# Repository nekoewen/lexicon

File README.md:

# Lexicon 65% Writing Keyboard

The Lexicon (or if you prefer the Lexicon 69 or the Cluney №3) is a 65% keyboard designed for writing prose, available from [WeirdLittleKeebs](https://www.weirdlittlekeebs.com/). With an extensive collection of shortcuts for words, formatting commands, and extended punctuation, this keyboard changes the experience of writing while maintaining a standard QWERTY layout. Check out the User's Guide to see how its unique features work.

## [Build Guide](https://github.com/nekoewen/lexicon/blob/main/Lexicon%20Build%20Guide.pdf)
If you purchased a set of Lexicon PCB and plates, this guide will walk you through the assembly process.

## [User's Guide](https://github.com/nekoewen/lexicon/blob/main/Lexicon%20User's%20Guide.pdf)
Once you have a Lexicon ready to use, this guide explains all of its features in detail.

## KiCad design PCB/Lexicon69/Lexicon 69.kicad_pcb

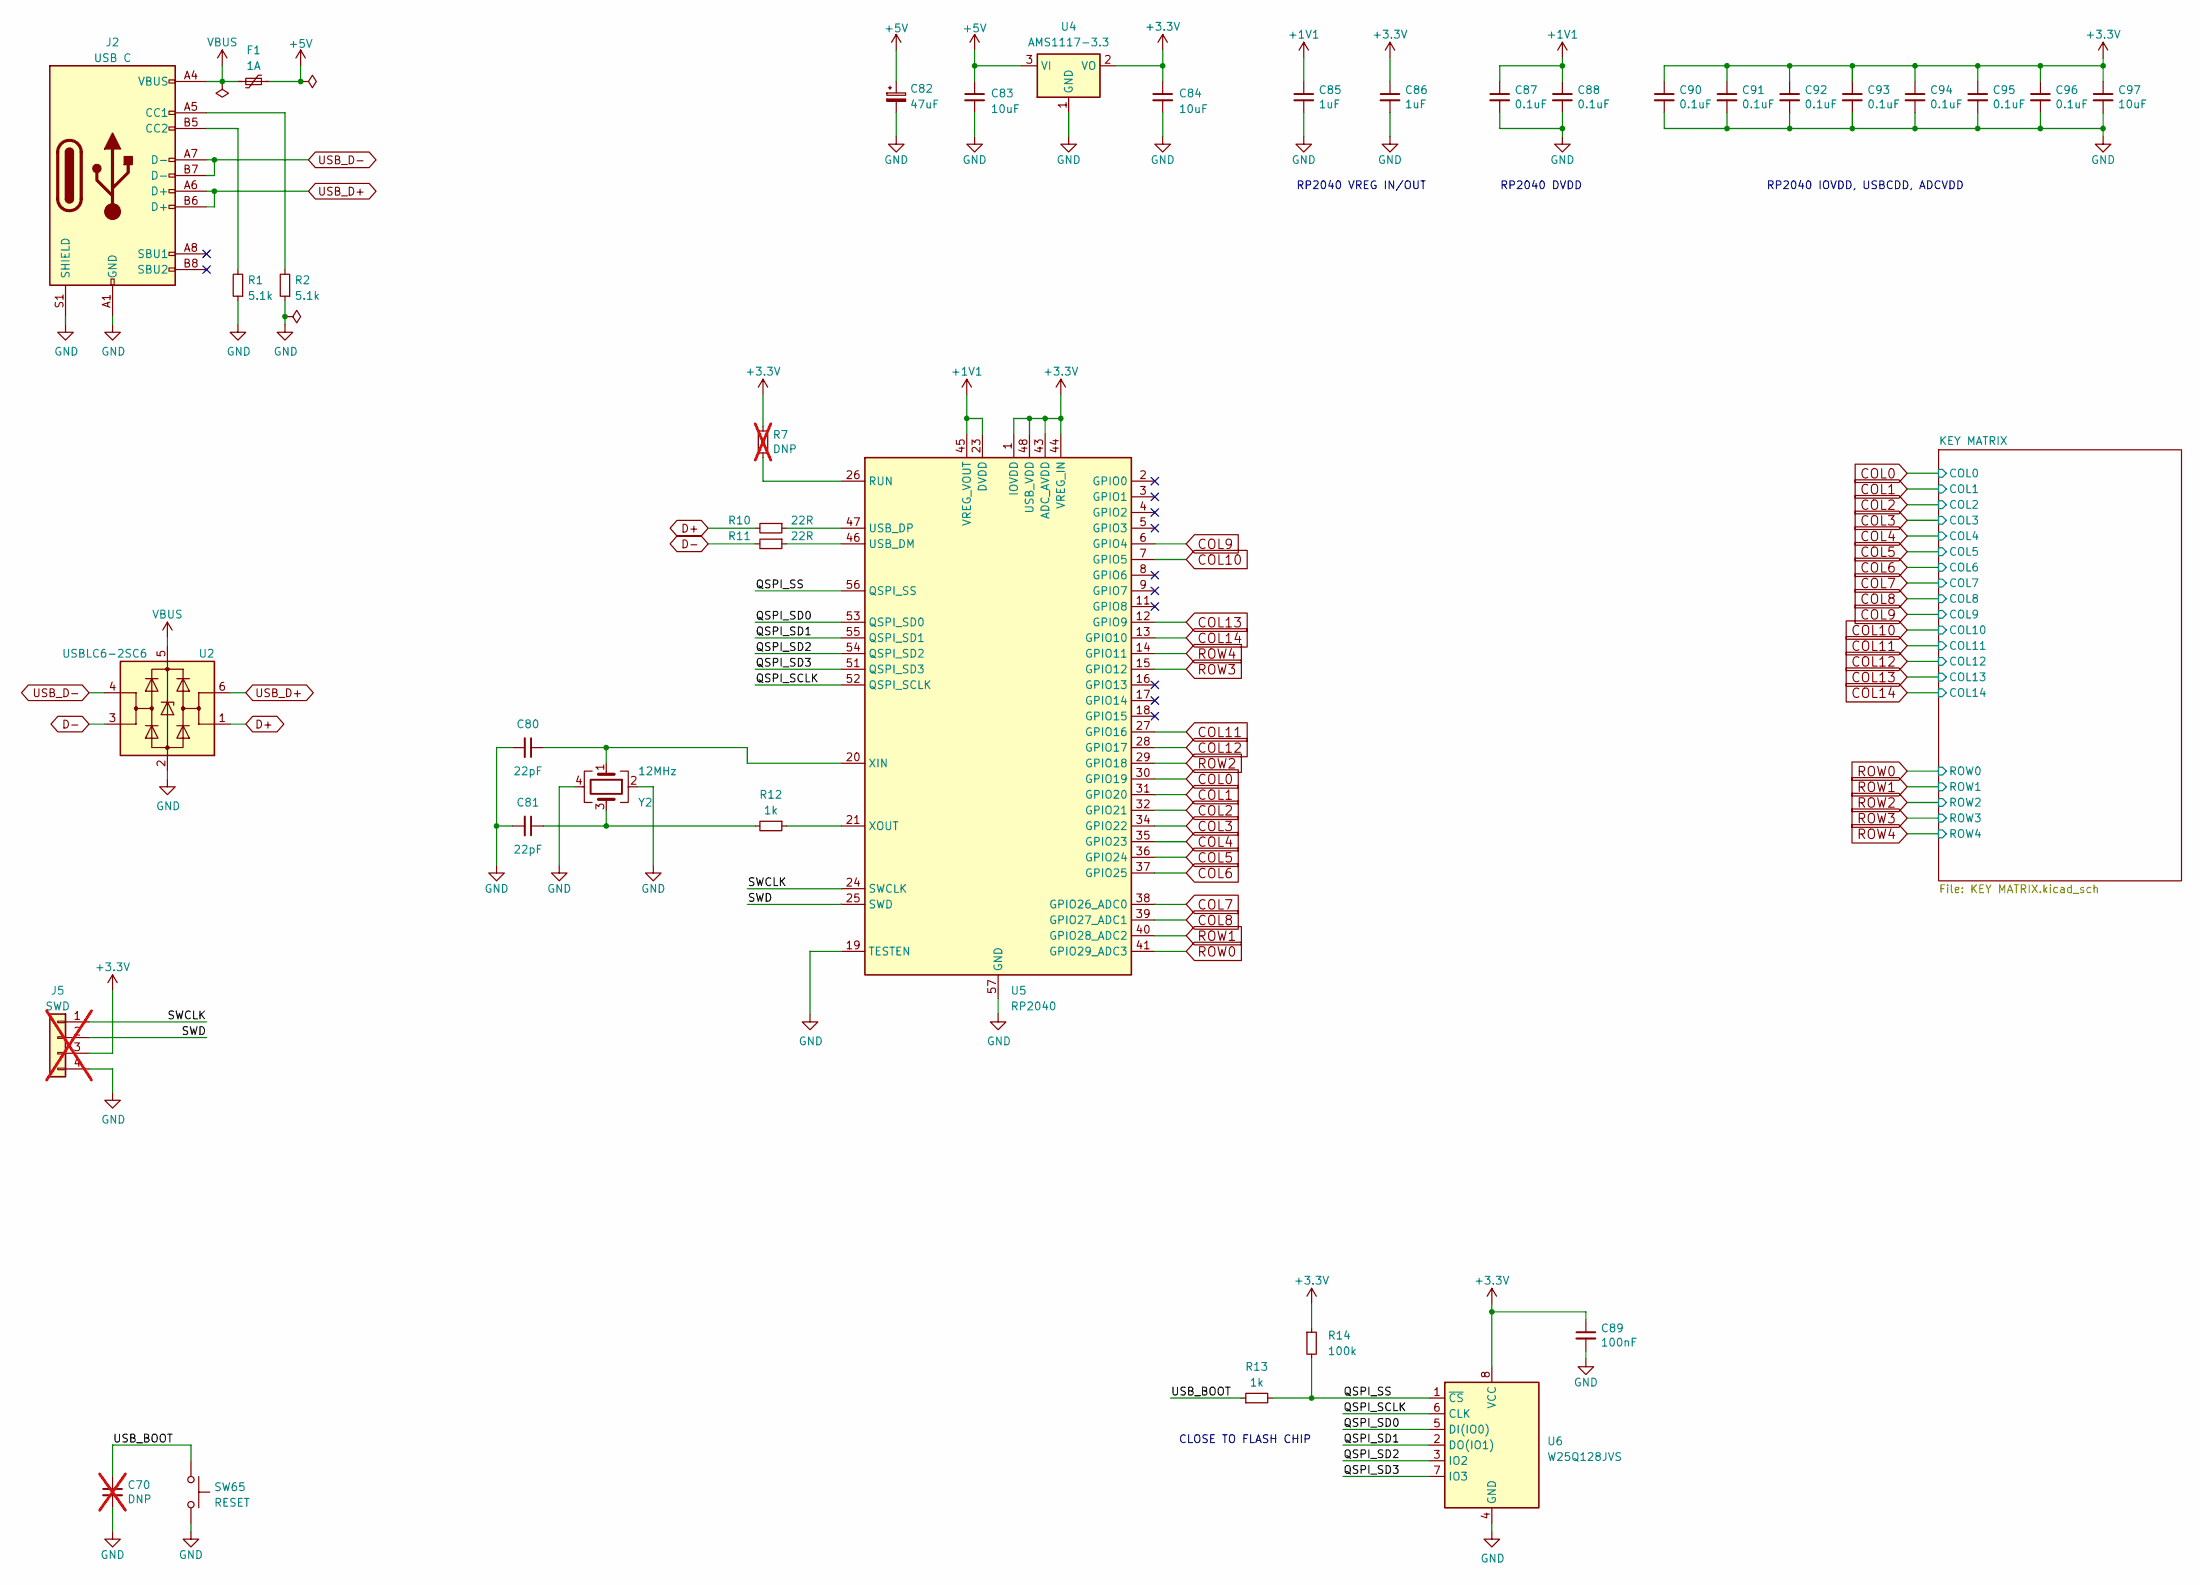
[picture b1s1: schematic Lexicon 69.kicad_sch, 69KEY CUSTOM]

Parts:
C70: DNP; C_0402_1005Metric; not fitted
C80, C81: 22pF; C_0402_1005Metric
C82: 47uF; CP_EIA-3216-10_Kemet-I
C83, C84, C97: 10uF; C_0805_2012Metric
C85, C86: 1uF; C_0402_1005Metric
C87, C88, C90, C91, C92, C93, C94, C95, C96: 0.1uF; C_0402_1005Metric
C89: 100nF; C_0402_1005Metric
F1: 1A; Fuse_0805_2012Metric
J2: USB C; USB_C_Receptacle_HRO_TYPE-C-31-M-12
J5: SWD; PinHeader_1x04_P2.54mm_Vertical; not fitted
R1, R2: 5.1k; R_0402_1005Metric
R7: DNP; R_0402_1005Metric; not fitted
R10, R11: 22R; R_0402_1005Metric
R12, R13: 1k; R_0402_1005Metric
R14: 100k; R_0402_1005Metric
SW65: RESET; SW_SPST_SKQG_WithStem
U2: USBLC6-2SC6; SOT-23-6
U4: AMS1117-3.3; SOT-223-3_TabPin2
U5: RP2040; QFN-56-1EP_7x7mm_P0.4mm_EP3.2x3.2mm
U6: W25Q128JVS; SOIC-8_5.23x5.23mm_P1.27mm
Y2: 12MHz; Crystal_SMD_SeikoEpson_FA238-4Pin_3.2x2.5mm

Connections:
+1V1: C85.1, C87.1, C88.1, U5.23 (DVDD), U5.45 (VREG_VOUT), U5.50 (DVDD)
+3.3V: C84.1, C86.1, C89.1, C90.1, C91.1, C92.1, C93.1, C94.1, C95.1, C96.1, C97.1, J5.3, R7.1, R14.1, U4.2 (VO), U5.1 (IOVDD), U5.10 (IOVDD), U5.22 (IOVDD), U5.33 (IOVDD), U5.42 (IOVDD), U5.43 (ADC_AVDD), U5.44 (VREG_IN), U5.48 (USB_VDD), U5.49 (IOVDD), U6.8 (VCC)
+5V: C82.1, C83.1, F1.1, U4.3 (VI)
/QSPI_SCLK: U5.52 (QSPI_SCLK), U6.6 (CLK)
/QSPI_SD0: U5.53 (QSPI_SD0), U6.5 (DI(IO0))
/QSPI_SD1: U5.55 (QSPI_SD1), U6.2 (DO(IO1))
/QSPI_SD2: U5.54 (QSPI_SD2), U6.3 (IO2)
/QSPI_SD3: U5.51 (QSPI_SD3), U6.7 (IO3)
/QSPI_SS: R13.2, R14.2, U5.56 (QSPI_SS), U6.1 (~CS)
/SWCLK: J5.1, U5.24 (SWCLK)
/SWD: J5.2, U5.25 (SWD)
/USB_BOOT: C70.1, R13.1, SW65.1
COL0: U5.30 (GPIO19); also elsewhere on the board
COL1: U5.31 (GPIO20); also elsewhere on the board
COL2: U5.32 (GPIO21); also elsewhere on the board
COL3: U5.34 (GPIO22); also elsewhere on the board
COL4: U5.35 (GPIO23); also elsewhere on the board
COL5: U5.36 (GPIO24); also elsewhere on the board
COL6: U5.37 (GPIO25); also elsewhere on the board
COL7: U5.38 (GPIO26_ADC0); also elsewhere on the board
COL8: U5.39 (GPIO27_ADC1); also elsewhere on the board
COL9: U5.6 (GPIO4); also elsewhere on the board
COL10: U5.7 (GPIO5); also elsewhere on the board
COL11: U5.27 (GPIO16); also elsewhere on the board
COL12: U5.28 (GPIO17); also elsewhere on the board
COL13: U5.12 (GPIO9); also elsewhere on the board
COL14: U5.13 (GPIO10); also elsewhere on the board
D+: R10.2, U2.1 (I/O1)
D-: R11.2, U2.3 (I/O2)
GND: C70.2, C80.2, C81.2, C82.2, C83.2, C84.2, C85.2, C86.2, C87.2, C88.2, C89.2, C90.2, C91.2, C92.2, C93.2, C94.2, C95.2, C96.2, C97.2, J2.A1 (GND), J2.A12 (GND), J2.B1 (GND), J2.B12 (GND), J2.S1 (SHIELD), J5.4, R1.1, R2.1, SW65.2, U2.2 (GND), U4.1 (GND), U5.19 (TESTEN), U5.57 (GND), U6.4 (GND), Y2.2, Y2.4
unnamed: C81.1, R12.2, Y2.3
unnamed: J2.A5 (CC1), R2.2
unnamed: J2.B5 (CC2), R1.2
unnamed: R7.2, U5.26 (RUN)
unnamed: R11.1, U5.46 (USB_DM)
unnamed: R10.1, U5.47 (USB_DP)
unnamed: C80.1, U5.20 (XIN), Y2.1
unnamed: R12.1, U5.21 (XOUT)
ROW0: U5.41 (GPIO29_ADC3); also elsewhere on the board
ROW1: U5.40 (GPIO28_ADC2); also elsewhere on the board
ROW2: U5.29 (GPIO18); also elsewhere on the board
ROW3: U5.15 (GPIO12); also elsewhere on the board
ROW4: U5.14 (GPIO11); also elsewhere on the board
USB_D+: J2.A6 (D+), J2.B6 (D+), U2.6 (I/O1)
USB_D-: J2.A7 (D-), J2.B7 (D-), U2.4 (I/O2)
VBUS: F1.2, J2.A4 (VBUS), J2.A9 (VBUS), J2.B4 (VBUS), J2.B9 (VBUS), U2.5 (VBUS)

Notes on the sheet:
RP2040 IOVDD, USBCDD, ADCVDD
RP2040 VREG IN/OUT
CLOSE TO FLASH CHIP
RP2040 DVDD

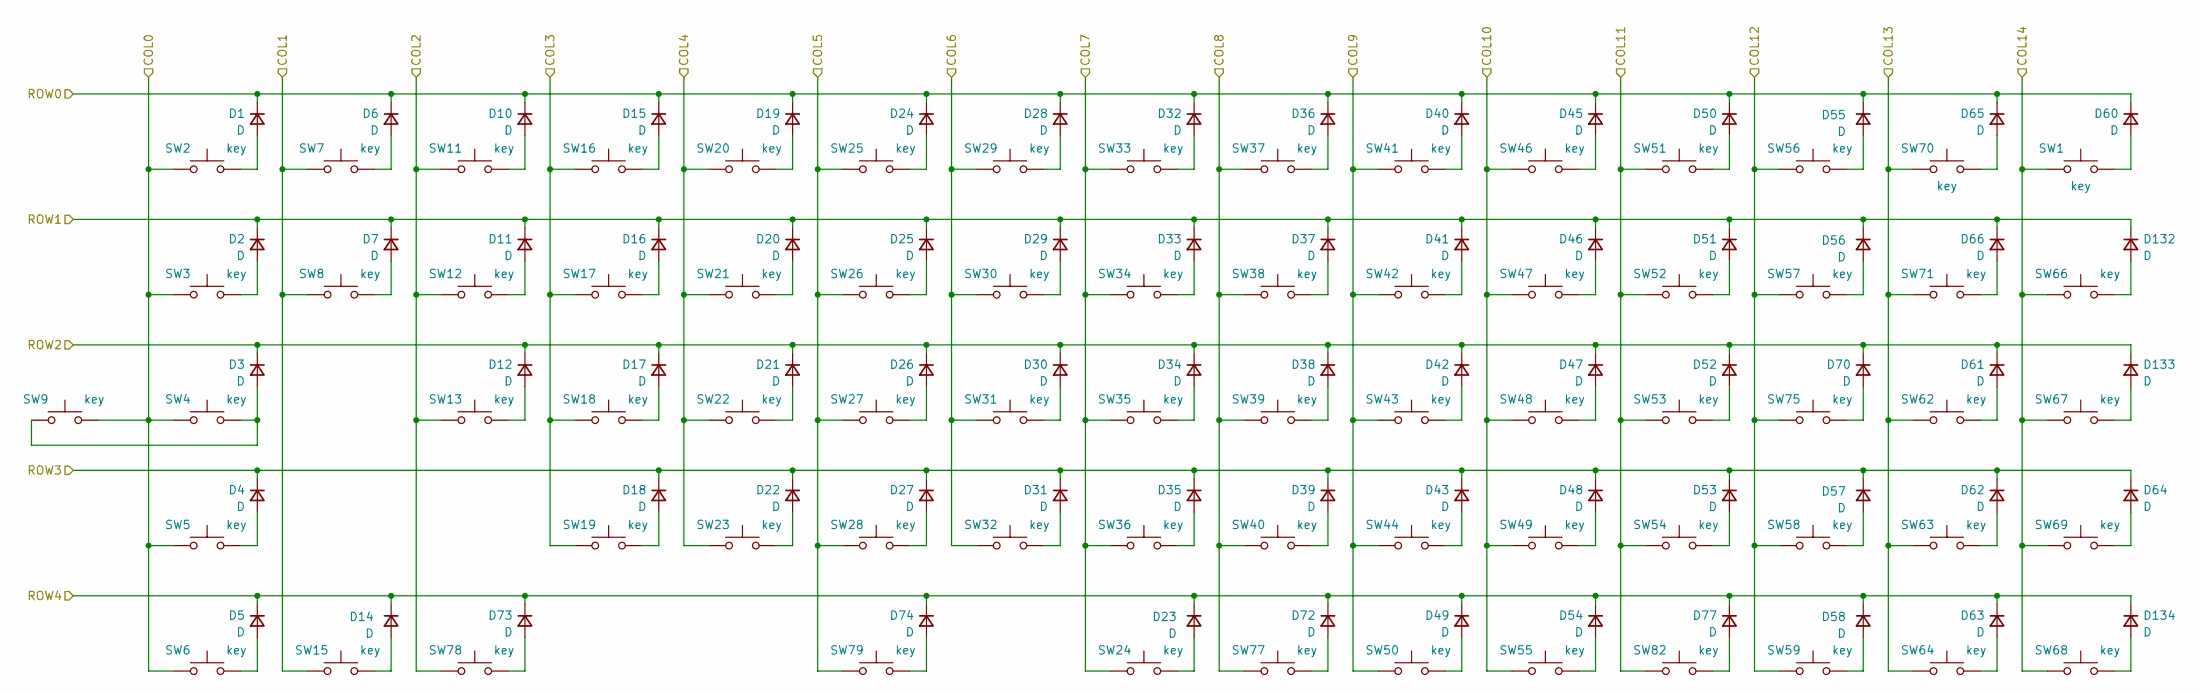
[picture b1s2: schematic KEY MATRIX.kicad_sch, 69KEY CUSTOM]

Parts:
D1, D2, D3, D4, D5, D6, D7, D10, D11, D12, D14, D15, D16, D17, D18, D19, D20, D21, D22, D23, D24, D25, D26, D27, D28, D29, D30, D31, D32, D33, D34, D35, D36, D37, D38, D39, D40, D41, D42, D43, D45, D46, D47, D48, D49, D50, D51, D52, D53, D54, D55, D56, D57, D58, D60, D61, D62, D63, D64, D65, D66, D70, D72, D73, D74, D77, D132, D133, D134: D; SOD-123
SW1, SW2, SW3, SW4, SW5, SW6, SW7, SW8, SW9, SW11, SW12, SW13, SW15, SW16, SW17, SW18, SW19, SW20, SW21, SW22, SW23, SW24, SW25, SW26, SW27, SW28, SW29, SW30, SW31, SW32, SW33, SW34, SW35, SW36, SW37, SW38, SW39, SW40, SW41, SW42, SW43, SW44, SW46, SW47, SW48, SW49, SW50, SW51, SW52, SW53, SW54, SW55, SW56, SW57, SW58, SW59, SW62, SW63, SW64, SW66, SW67, SW68, SW69, SW70, SW71, SW75, SW77, SW78, SW79, SW82: key; SW_Cherry_MX_1.00u_PCB

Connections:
COL0: SW2.1, SW3.1, SW4.1, SW5.1, SW6.1, SW9.2; also elsewhere on the board
COL1: SW7.1, SW8.1, SW15.1; also elsewhere on the board
COL2: SW11.1, SW12.1, SW13.1, SW78.1; also elsewhere on the board
COL3: SW16.1, SW17.1, SW18.1, SW19.1; also elsewhere on the board
COL4: SW20.1, SW21.1, SW22.1, SW23.1; also elsewhere on the board
COL5: SW25.1, SW26.1, SW27.1, SW28.1, SW79.1; also elsewhere on the board
COL6: SW29.1, SW30.1, SW31.1, SW32.1; also elsewhere on the board
COL7: SW24.1, SW33.1, SW34.1, SW35.1, SW36.1; also elsewhere on the board
COL8: SW37.1, SW38.1, SW39.1, SW40.1, SW77.1; also elsewhere on the board
COL9: SW41.1, SW42.1, SW43.1, SW44.1, SW50.1; also elsewhere on the board
COL10: SW46.1, SW47.1, SW48.1, SW49.1, SW55.1; also elsewhere on the board
COL11: SW51.1, SW52.1, SW53.1, SW54.1, SW82.1; also elsewhere on the board
COL12: SW56.1, SW57.1, SW58.1, SW59.1, SW75.1; also elsewhere on the board
COL13: SW62.1, SW63.1, SW64.1, SW70.1, SW71.1; also elsewhere on the board
COL14: SW1.1, SW66.1, SW67.1, SW68.1, SW69.1; also elsewhere on the board
unnamed: D1.2 (A), SW2.2
unnamed: D2.2 (A), SW3.2
unnamed: D3.2 (A), SW4.2, SW9.1
unnamed: D4.2 (A), SW5.2
unnamed: D5.2 (A), SW6.2
unnamed: D6.2 (A), SW7.2
unnamed: D7.2 (A), SW8.2
unnamed: D10.2 (A), SW11.2
unnamed: D11.2 (A), SW12.2
unnamed: D12.2 (A), SW13.2
unnamed: D14.2 (A), SW15.2
unnamed: D15.2 (A), SW16.2
unnamed: D16.2 (A), SW17.2
unnamed: D17.2 (A), SW18.2
unnamed: D18.2 (A), SW19.2
unnamed: D19.2 (A), SW20.2
unnamed: D20.2 (A), SW21.2
unnamed: D21.2 (A), SW22.2
unnamed: D22.2 (A), SW23.2
unnamed: D23.2 (A), SW24.2
unnamed: D24.2 (A), SW25.2
unnamed: D25.2 (A), SW26.2
unnamed: D26.2 (A), SW27.2
unnamed: D27.2 (A), SW28.2
unnamed: D28.2 (A), SW29.2
unnamed: D29.2 (A), SW30.2
unnamed: D30.2 (A), SW31.2
unnamed: D31.2 (A), SW32.2
unnamed: D32.2 (A), SW33.2
unnamed: D33.2 (A), SW34.2
unnamed: D34.2 (A), SW35.2
unnamed: D35.2 (A), SW36.2
unnamed: D36.2 (A), SW37.2
unnamed: D37.2 (A), SW38.2
unnamed: D38.2 (A), SW39.2
unnamed: D39.2 (A), SW40.2
unnamed: D40.2 (A), SW41.2
unnamed: D41.2 (A), SW42.2
unnamed: D42.2 (A), SW43.2
unnamed: D43.2 (A), SW44.2
unnamed: D45.2 (A), SW46.2
unnamed: D46.2 (A), SW47.2
unnamed: D47.2 (A), SW48.2
unnamed: D48.2 (A), SW49.2
unnamed: D49.2 (A), SW50.2
unnamed: D50.2 (A), SW51.2
unnamed: D51.2 (A), SW52.2
unnamed: D52.2 (A), SW53.2
unnamed: D53.2 (A), SW54.2
unnamed: D54.2 (A), SW55.2
unnamed: D55.2 (A), SW56.2
unnamed: D56.2 (A), SW57.2
unnamed: D57.2 (A), SW58.2
unnamed: D58.2 (A), SW59.2
unnamed: D60.2 (A), SW1.2
unnamed: D61.2 (A), SW62.2
unnamed: D62.2 (A), SW63.2
unnamed: D63.2 (A), SW64.2
unnamed: D64.2 (A), SW69.2
unnamed: D65.2 (A), SW70.2
unnamed: D66.2 (A), SW71.2
unnamed: D70.2 (A), SW75.2
unnamed: D72.2 (A), SW77.2
unnamed: D73.2 (A), SW78.2
unnamed: D74.2 (A), SW79.2
unnamed: D77.2 (A), SW82.2
unnamed: D132.2 (A), SW66.2
unnamed: D133.2 (A), SW67.2
unnamed: D134.2 (A), SW68.2
ROW0: D1.1 (K), D6.1 (K), D10.1 (K), D15.1 (K), D19.1 (K), D24.1 (K), D28.1 (K), D32.1 (K), D36.1 (K), D40.1 (K), D45.1 (K), D50.1 (K), D55.1 (K), D60.1 (K), D65.1 (K); also elsewhere on the board
ROW1: D2.1 (K), D7.1 (K), D11.1 (K), D16.1 (K), D20.1 (K), D25.1 (K), D29.1 (K), D33.1 (K), D37.1 (K), D41.1 (K), D46.1 (K), D51.1 (K), D56.1 (K), D66.1 (K), D132.1 (K); also elsewhere on the board
ROW2: D3.1 (K), D12.1 (K), D17.1 (K), D21.1 (K), D26.1 (K), D30.1 (K), D34.1 (K), D38.1 (K), D42.1 (K), D47.1 (K), D52.1 (K), D61.1 (K), D70.1 (K), D133.1 (K); also elsewhere on the board
ROW3: D4.1 (K), D18.1 (K), D22.1 (K), D27.1 (K), D31.1 (K), D35.1 (K), D39.1 (K), D43.1 (K), D48.1 (K), D53.1 (K), D57.1 (K), D62.1 (K), D64.1 (K); also elsewhere on the board
ROW4: D5.1 (K), D14.1 (K), D23.1 (K), D49.1 (K), D54.1 (K), D58.1 (K), D63.1 (K), D72.1 (K), D73.1 (K), D74.1 (K), D77.1 (K), D134.1 (K); also elsewhere on the board

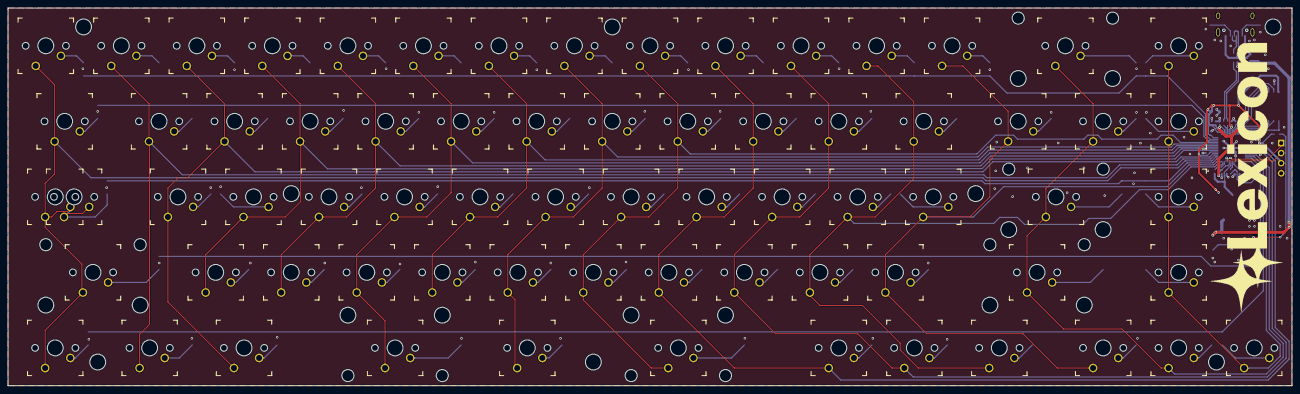
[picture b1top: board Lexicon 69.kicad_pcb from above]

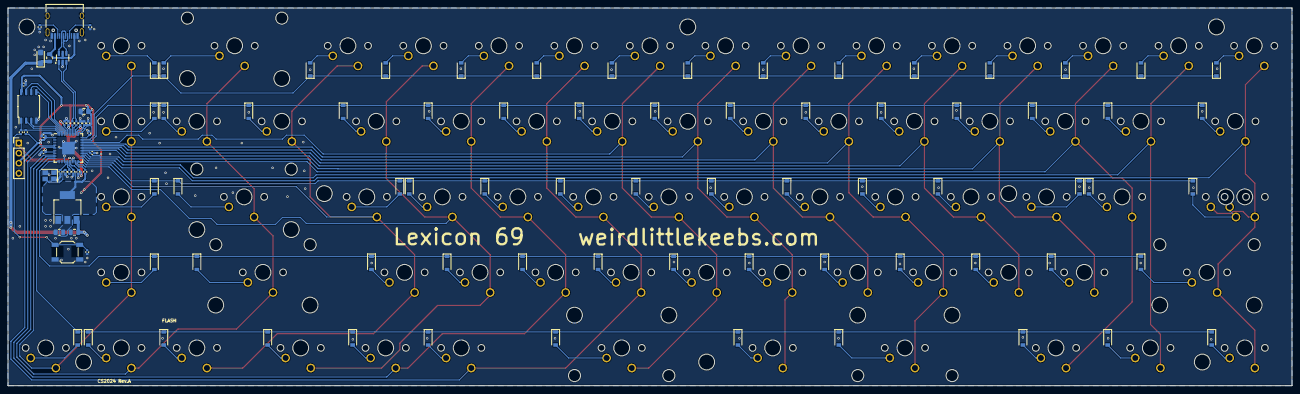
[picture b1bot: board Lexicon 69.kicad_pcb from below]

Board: 2 copper layers, 323.9 x 95.2 mm, 175 parts (105 on the bottom side), 115 nets.

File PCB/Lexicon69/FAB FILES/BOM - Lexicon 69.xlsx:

Designator | Comment | Footprint | LCSC Part #
C80, C81 | 22pF | 402 | C1563
C82 | 47uF | 3216 | C131173
C83, C84, C97 | 10uF | 805 | C15850
C85, C86 | 1uF | 402 | C52923
C87, C88, C90, C91, C92, C93, C94, C95, C96 | 0.1uF | 402 | C1525
C89 | 100nF | 402 | C1525
D1, D2, D3, D4, D5, D6, D7, D10, D11, D12, D14, D15, D16, D17, D18, D19, D20, D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 | D | SOD-123 | C81598
F1 | 1A | 805 | C883105
J2 | USB C | SMD | C165948
R1, R2 | 5.1k | 402
R10, R11 | 22R | 402
R12, R13 | 1k | 402
R14 | 100k | 402
SW65 | RESET | Button_Switch_SMD:SW_SPST_SKQG_WithStem | C318884
U2 | USBLC6-2SC6 | SOT-23-6 | C7519
U4 | AMS1117-3.3 | SOT-223-3 | C6186
U5 | RP2040 | LQFN-56(7x7) | C2040
U6 | W25Q128JVS | SOIC-8-208mil | C97521
Y2 | 12MHz | SMD3225-4P | C9002

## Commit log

2024-06-24 Create userguide
2024-06-24 Rename userguide to userguide.md
2025-01-26 Create LICENSE
2026-02-11 Add readme for Lexicon Case project
2026-02-11 Add image to case readme
    Added an image to the readme for visual reference.
2026-02-11 Change image format in readme
    Updated image file extension from .jpg to .jpeg.

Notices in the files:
README.md:
License: CC BY-NC-SA 4.0
